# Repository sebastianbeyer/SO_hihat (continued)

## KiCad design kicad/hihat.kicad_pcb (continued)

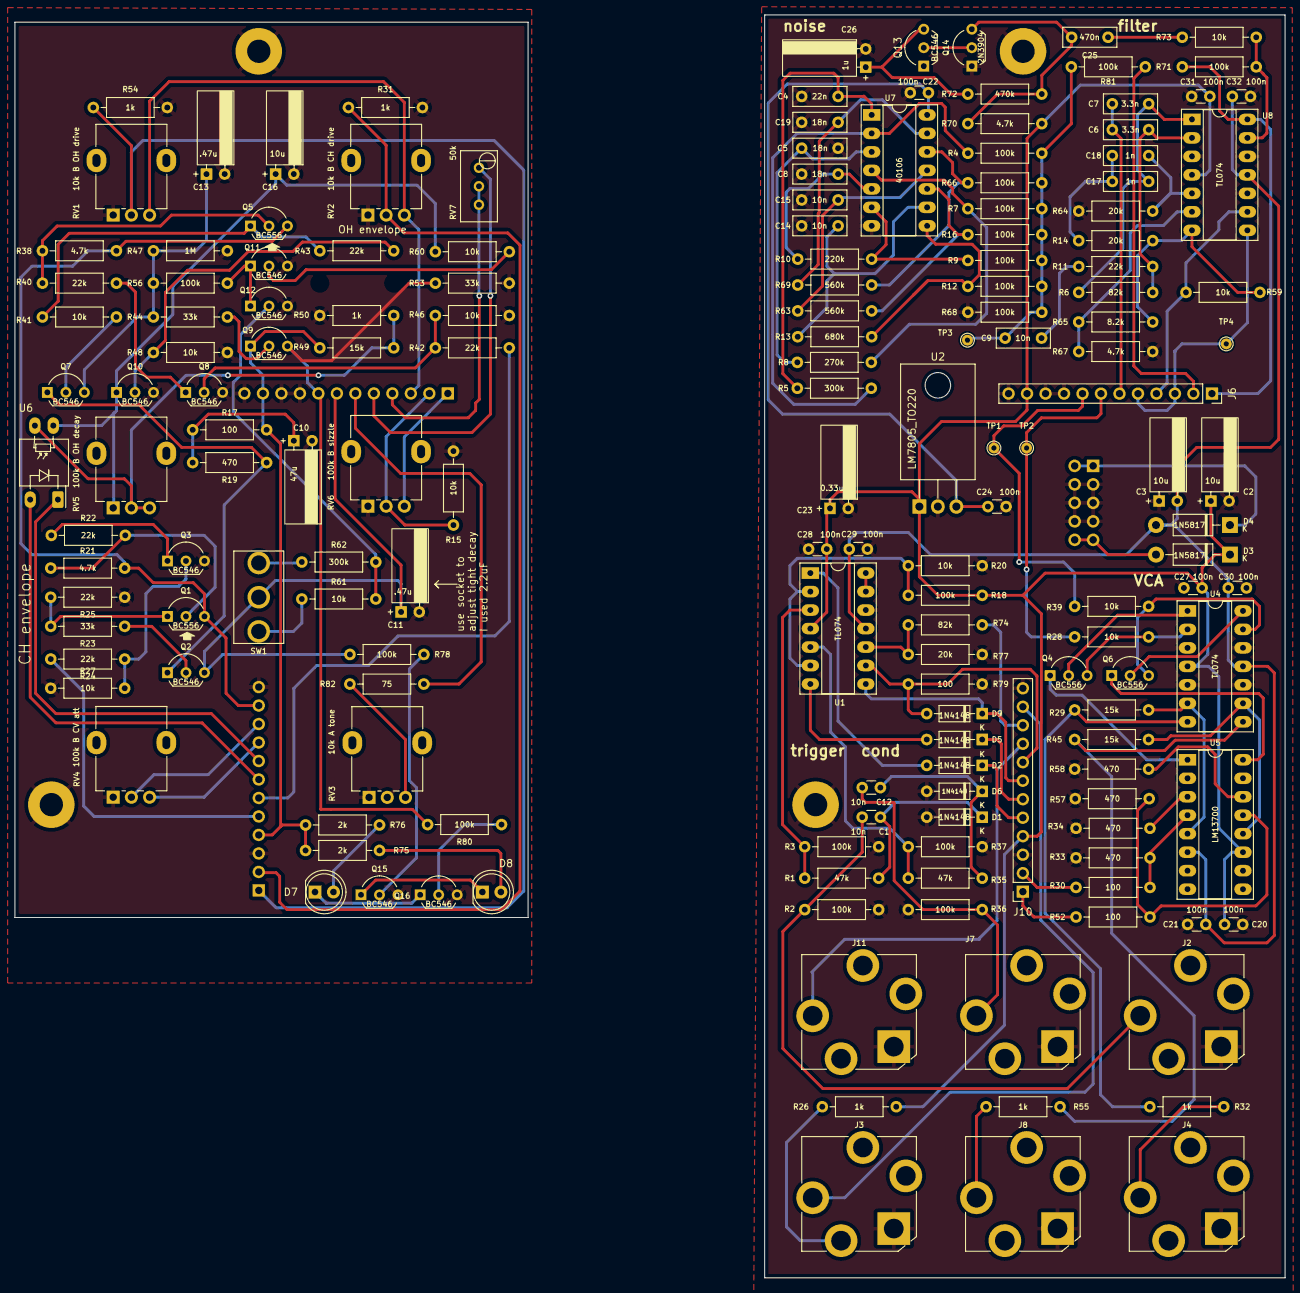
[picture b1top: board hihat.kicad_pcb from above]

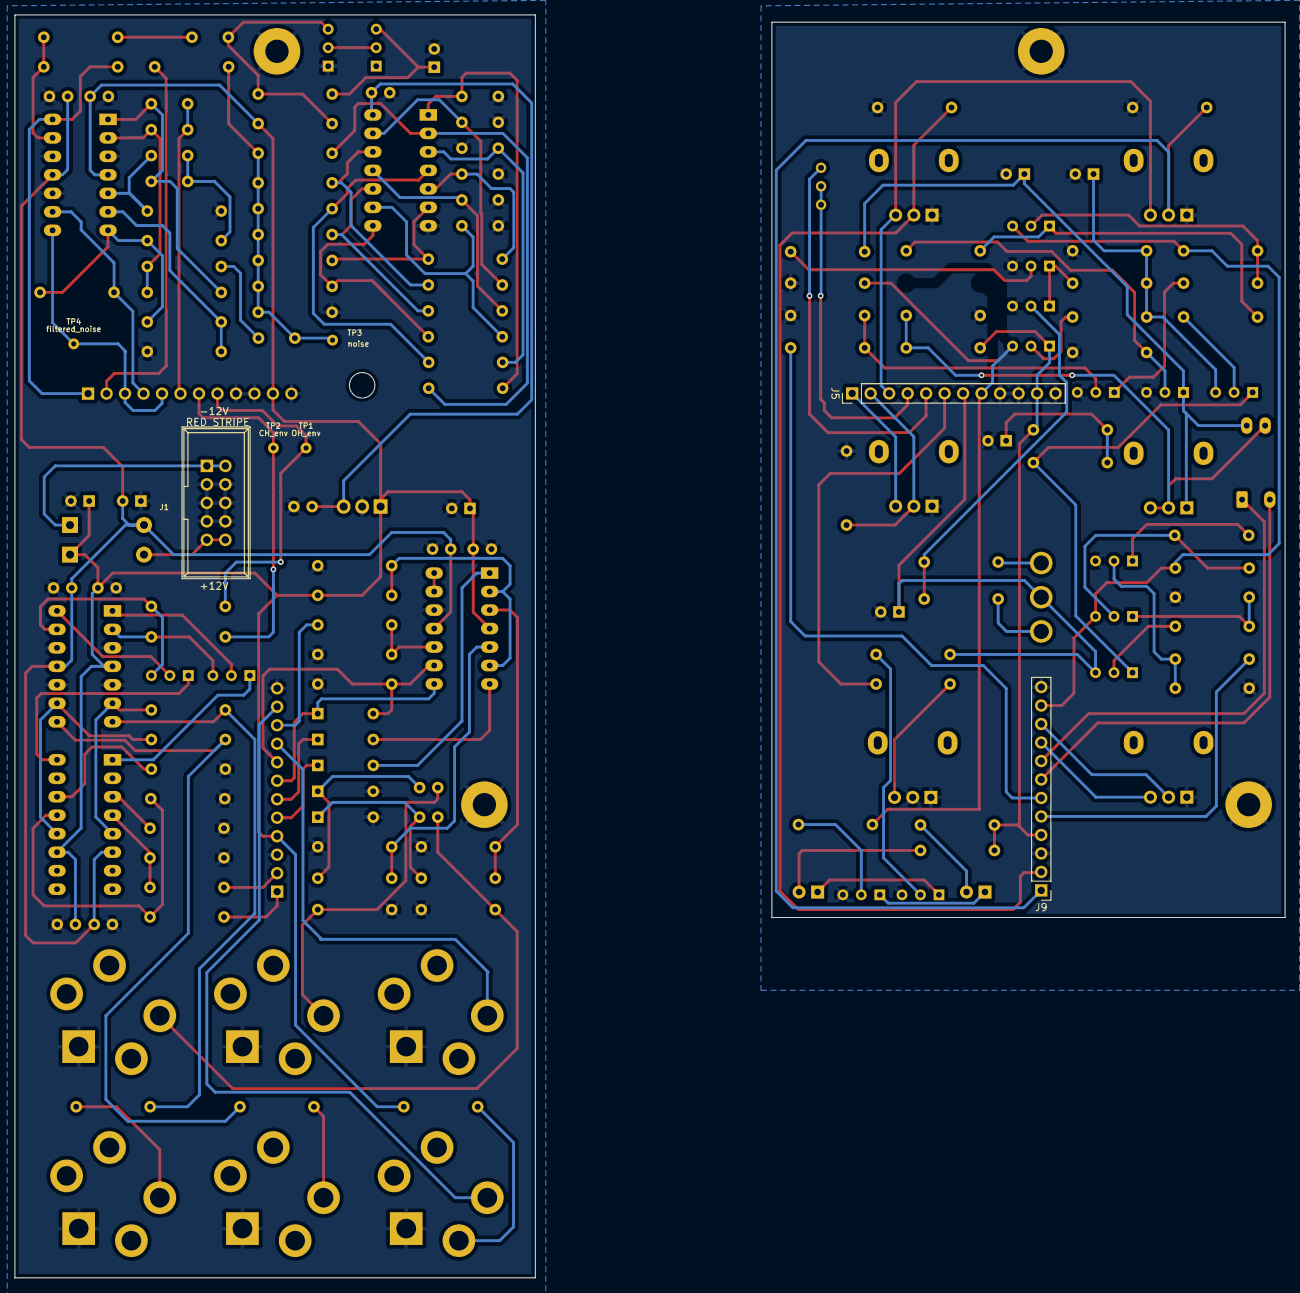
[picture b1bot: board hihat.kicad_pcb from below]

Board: 2 copper layers, 174.5 x 173.5 mm, 172 parts (3 on the bottom side), 121 nets.

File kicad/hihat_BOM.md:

# hihat.kicad_sch BOM

Tue 22 Nov 2022 12:08:40 CET

Generated from schematic by Eeschema 6.0.8-f2edbf62ab~116~ubuntu22.04.1

**Component Count:** 168

| Refs | Qty | Component | Description | Vendor | SKU |
| ----- | --- | ---- | ----------- | ---- | ---- |
| C1, C12 | 2 | 10n | Unpolarized capacitor | Tayda |  |
| C2, C3, C16 | 3 | 10u | Polarized capacitor | Tayda |  |
| C4 | 1 | 22n | Unpolarized capacitor | Tayda |  |
| C5, C8, C19 | 3 | 18n | Unpolarized capacitor | Tayda |  |
| C6, C7 | 2 | 3.3n | Unpolarized capacitor | Tayda |  |
| C9, C14, C15 | 3 | 10n | Unpolarized capacitor | Tayda |  |
| C10 | 1 | 47u | Polarized capacitor | Tayda |  |
| C11, C13 | 2 | .47u | Polarized capacitor | Tayda |  |
| C17, C18 | 2 | 1n | Unpolarized capacitor | Tayda |  |
| C20, C21, C27, C28, C29, C30, C31, C32 | 8 | 100n | Unpolarized capacitor |  |  |
| C22, C24 | 2 | 100n | Unpolarized capacitor | Tayda |  |
| C23 | 1 | 0.33u | Polarized capacitor | Tayda |  |
| C25 | 1 | 470n | Unpolarized capacitor | Tayda |  |
| C26 | 1 | 1u | Polarized capacitor | Tayda |  |
| D1, D2, D5, D6, D9 | 5 | 1N4148 | Standard switching diode, DO-35 | Tayda | A-157 |
| D3, D4 | 2 | 1N5817 | Schottky Barrier Rectifier Diode, DO-41 | Tayda | A-159 |
| D7 | 1 | LED_red_OH | Light emitting diode | Tayda | A-1554 |
| D8 | 1 | LED_red_CH | Light emitting diode | Tayda | A-1554 |
| H1, H2, H3, H4 | 4 | MountingHole | Mounting Hole with connection |  |  |
| J1 | 1 | Synth_power_2x5 | Pin header 2.54 mm 2x5 | Tayda | A-2939 |
| J2 | 1 | CH trig | Audio Jack, 2 Poles (Mono / TS), Switched T Pole (Normalling) | Tayda | A-1121 |
| J3 | 1 | accent | Audio Jack, 2 Poles (Mono / TS), Switched T Pole (Normalling) | Tayda | A-1121 |
| J4 | 1 | CH out | Audio Jack, 2 Poles (Mono / TS), Switched T Pole (Normalling) | Tayda | A-1121 |
| J5 | 1 | ctrl_north | Generic connector, single row, 01x12, script generated (kicad-library-utils/schlib/autogen/connector/) |  |  |
| J6 | 1 | brain_north | Generic connector, single row, 01x12, script generated (kicad-library-utils/schlib/autogen/connector/) |  |  |
| J7 | 1 | OH trig | Audio Jack, 2 Poles (Mono / TS), Switched T Pole (Normalling) | Tayda | A-1121 |
| J8 | 1 | OH out | Audio Jack, 2 Poles (Mono / TS), Switched T Pole (Normalling) | Tayda | A-1121 |
| J9 | 1 | ctrl_south | Generic connector, single row, 01x12, script generated (kicad-library-utils/schlib/autogen/connector/) |  |  |
| J10 | 1 | brain_south | Generic connector, single row, 01x12, script generated (kicad-library-utils/schlib/autogen/connector/) |  |  |
| J11 | 1 | CVin | Audio Jack, 2 Poles (Mono / TS), Switched T Pole (Normalling) | Tayda | A-1121 |
| Q1, Q4, Q5, Q6 | 4 | BC556 | 0.1A Ic, 65V Vce, PNP Small Signal Transistor, TO-92 |  |  |
| Q2, Q3, Q7, Q8, Q9, Q10, Q11, Q12, Q15, Q16 | 10 | BC546 | 0.1A Ic, 65V Vce, Small Signal NPN Transistor, TO-92 |  |  |
| Q13 | 1 | BC546 | 0.1A Ic, 65V Vce, Small Signal NPN Transistor, TO-92 |  |  |
| Q14 | 1 | 2N3904 | Small Signal NPN Transistor, TO-92 | Tayda | A-111 |
| R1, R35 | 2 | 47k | Resistor | Tayda |  |
| R2, R3, R4, R7, R9, R12, R16, R18, R36, R37, R56, R66, R68, R71, R78, R80, R81 | 17 | 100k | Resistor | Tayda |  |
| R5, R62 | 2 | 300k | Resistor | Tayda |  |
| R6, R74 | 2 | 82k | Resistor | Tayda |  |
| R8 | 1 | 270k | Resistor | Tayda |  |
| R10 | 1 | 220k | Resistor | Tayda |  |
| R11, R22, R24, R25, R40, R42, R43 | 7 | 22k | Resistor | Tayda |  |
| R13 | 1 | 680k | Resistor | Tayda |  |
| R14, R64, R77 | 3 | 20k | Resistor | Tayda |  |
| R15, R20, R27, R28, R39, R41, R46, R48, R59, R60, R61, R73 | 12 | 10k | Resistor | Tayda |  |
| R17, R30, R52, R79 | 4 | 100 | Resistor | Tayda |  |
| R19, R33, R34, R57, R58 | 5 | 470 | Resistor | Tayda |  |
| R21, R38, R67, R70 | 4 | 4.7k | Resistor | Tayda |  |
| R23, R44, R53 | 3 | 33k | Resistor | Tayda |  |
| R26, R31, R32, R50, R54, R55 | 6 | 1k | Resistor | Tayda |  |
| R29, R45, R49 | 3 | 15k | Resistor | Tayda |  |
| R47 | 1 | 1M | Resistor | Tayda |  |
| R63, R69 | 2 | 560k | Resistor | Tayda |  |
| R65 | 1 | 8.2k | Resistor | Tayda |  |
| R72 | 1 | 470k | Resistor | Tayda |  |
| R75, R76 | 2 | 2k | Resistor | Tayda |  |
| R82 | 1 | 75 | Resistor | Tayda |  |
| RV1 | 1 | 10k B OH drive | Potentiometer | Tayda |  |
| RV2 | 1 | 10k B CH drive | Potentiometer | Tayda |  |
| RV3 | 1 | 10k A tone | Potentiometer | Tayda |  |
| RV4 | 1 | 100k B CV att | Potentiometer | Tayda |  |
| RV5 | 1 | 100k B OH decay | Potentiometer | Tayda |  |
| RV6 | 1 | 100k B sizzle | Potentiometer | Tayda |  |
| RV7 | 1 | 50k | Trim-potentiometer | Tayda |  |
| SW1 | 1 | mute | Switch, single pole double throw, center OFF position |  |  |
| U1, U4, U8 | 3 | TL074 | Quad operational amplifier, DIP-14 | Tayda | A-1138 |
| U2 | 1 | LM7805_TO220 | Positive 1A 35V Linear Regulator, Fixed Output 5V, TO-220 |  |  |
| U5 | 1 | LM13700 | Dual OTA, DIP-16 | Tayda | A-900 |
| U6 | 1 | Vactrol | Vactrol |  |  |
| U7 | 1 | 40106 | Hex Schmitt trigger inverter |  |  |

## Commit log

2022-01-16 initial
2022-01-16 gerber settings maybe?
2022-02-01 fix noise section (1uF instead of 10uF), location of switch jacks!!, add resistor to make sizzle pot log-like and add note to use socket for cap to adjust tight decay
2022-02-01 probably only timestamp
2022-02-01 add resistor reference
2022-02-02 remove R51, now the open hat is much louder!
2022-02-02 add spice files to git
2022-02-02 change resistors in filter 18k to 20k
2022-11-22 add BOM
